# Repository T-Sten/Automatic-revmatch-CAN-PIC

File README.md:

# OPEL-automatic-revmatch-project

Hi! This is a project on creating a device that by plugging into a car's CAN buses and thottle pedal signals, is able to match the
engine RPMs of the lower gear to the wheel speed during a downshift, known as "Revmatching".
The operation of the device is controlled by a PIC16F877A MCU from Microchip.

### Basic idea
The basic idea is as follows: 
Steering wheel button pressed -> Wait for clutch disengagement -> Raise engine RPM to match the lower gear at the current speed and keep it there
-> Wait for clutch engagement -> Stop.

### CAN bus data
From the 3 CAN buses of my 2005 OPEL Vectra C we are interested in 2 of them: 95kbps low speed bus from where driver input can be read 
(such as steering wheel buttons for activating revmatching mode) and the 500kbps bus from where vehicle telematics data can be read
(such as engine RPM, vehicle speed, clucth state etc.). The vehicles CAN buses will be interfaced with a MCP2515 CAN controller IC
and a MCP2551 CAN transciever IC for each of the 2 buses.

### Controlling the throttle
Throttle is controlled by tapping into the (2) throttle pedal potentiometer output wires and with a signal relay we can disconnect
the thottle pedal outputs and start driving the signal voltage with a capacitor smooothed PWM signal to be interpreted by the ECU.
Throttle value is calculated using PID control.

### Additional features
Additional features of the device include displaying current gear on the dashboard with a 7-segment led and a led array for the current RPM. 
These are driven by 2 8-bit shift registers that are interfaced by the MCU with a single differential pair using a RS485 transciever.
Another feature is "welcome actions" where upon unlocking the car doors, horn is briefly activated 3 times
and high beams flashed. This is done by replicating driver input by sending a CAN frame that corresponds to the activation of their driver controls.

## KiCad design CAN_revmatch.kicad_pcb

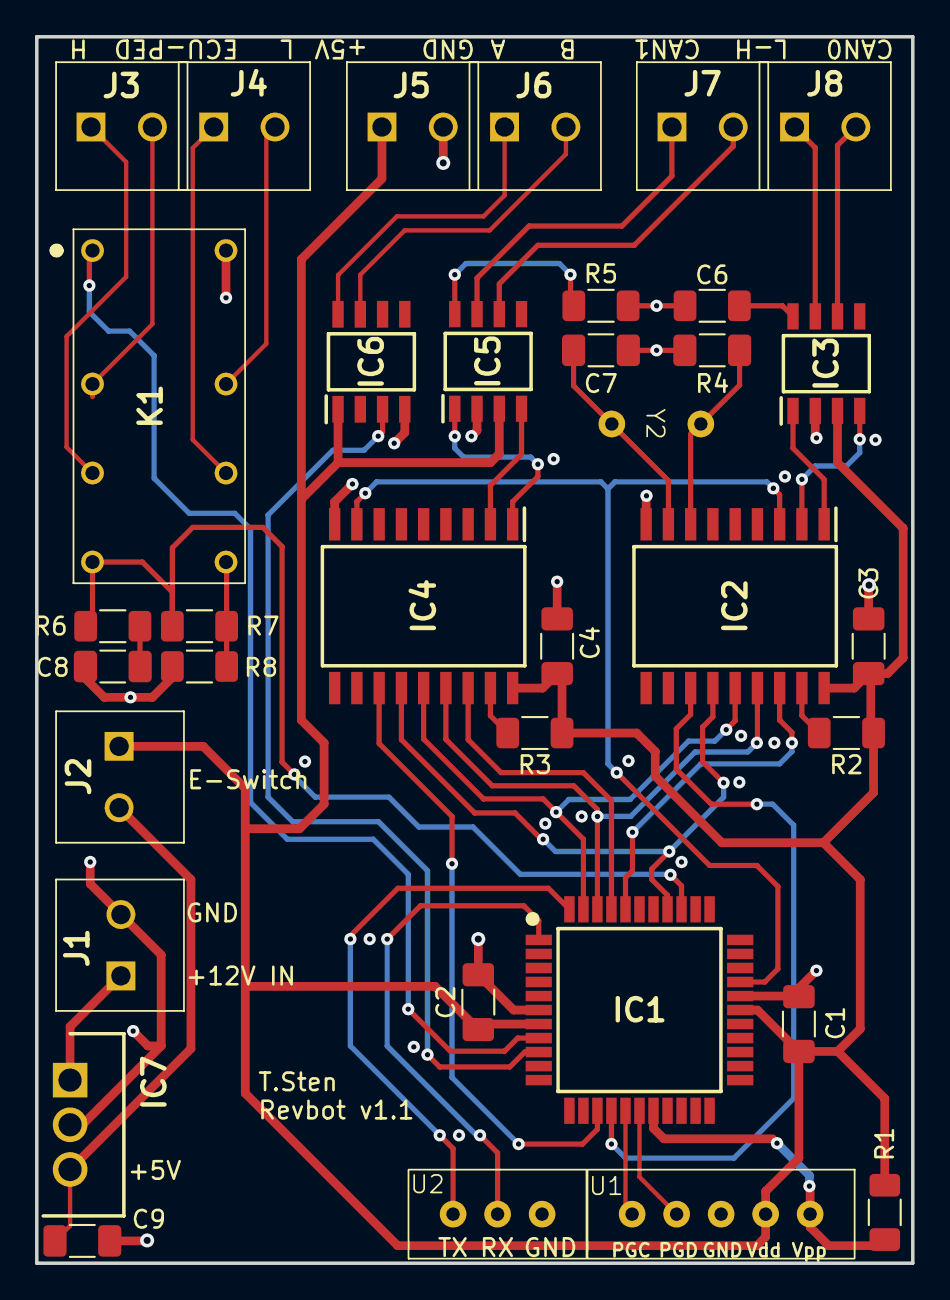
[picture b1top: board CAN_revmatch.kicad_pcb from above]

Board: 4 copper layers, 50.0 x 70.0 mm, 35 parts (0 on the bottom side), 42 nets.

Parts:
C1, C2, C3, C4: 100nF; C_1206_3216Metric_Pad1.33x1.80mm_HandSolder
C6, C7: 22pF; C_1206_3216Metric_Pad1.33x1.80mm_HandSolder
C8: 1uF; C_1206_3216Metric_Pad1.33x1.80mm_HandSolder
C9: 10uF; C_1206_3216Metric_Pad1.33x1.80mm_HandSolder
IC1: PIC16F877A-I_PT; PIC16F877A-SOIC-44pin
IC2, IC4: MCP2515-I_SO; MCP2515_SOIC
IC3, IC5: MCP2551-I_SN; MCP2551_SOIC
IC6: SN75179BDR; Transciever_SN75179BDR
IC7: L7805CV
J1: Power terminal; 1888807
J2: E-Switch; 1888807
J3: Throttle_H; 1888807
J4: Throttle_L; 1888807
J5: RPM/GEAR disp. power; 1888807
J6: RPM/GEAR disp. data; 1888807
J7: CAN1 terminal; 1888807
J8: CAN0 terminal; 1888807
K1: RY-5W-K; RY5WK
R1, R2, R3, R4, R5: 10k; R_1206_3216Metric_Pad1.30x1.75mm_HandSolder
R6, R7, R8: 4.7k; R_1206_3216Metric_Pad1.30x1.75mm_HandSolder
U1: Pickit terminal pin header male; PICKIT_terminal
U2: UART pin header female; UART_terminal
Y2: 8MHz; KIDE

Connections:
+5V: C1.1, C2.1, C3.1, C4.1, IC1.7 (VDD_1), IC1.28 (VDD_2), IC2.18 (VDD), IC3.3 (VDD), IC4.18 (VDD), IC5.3 (VDD), IC6.1 (VCC), J2.1, J5.1, R1.2, R2.1, R3.1, U1.2 (Vdd)
/CLOCK: IC1.30 (OSC1/CLKI), IC2.3 (CLKOUT/SOF), IC4.8 (OSC1)
/CS_CAN0: IC1.40 (RD2/PSP2), IC2.16 (~CS)
/CS_CAN1: IC1.41 (RD3/PSP3), IC4.16 (~CS)
/INT_CAN0: IC1.15 (RB5), IC2.12 (~INT)
/INT_CAN1: IC1.14 (RB4), IC4.12 (~INT)
/MISO: IC1.42 (RC4/SDI/SDA), IC2.15 (SO), IC4.15 (SO)
/MOSI: IC1.43 (RC5/SDO), IC2.14 (SI), IC4.14 (SI)
/PWM: IC1.36 (RC2/CCP1), K1.8, R6.1, R7.2
/RELAY_COIL: IC1.8 (RB0/INT), K1.1
/SCK: IC1.37 (RC3/SCK/SCL), IC2.13 (SCK), IC4.13 (SCK)
/SN75179B_D: IC1.9 (RB1), IC6.3 (D)
GND: C1.2, C2.2, C3.2, C4.2, C6.2, C7.2, C8.2, C9.2, IC1.6 (VSS_1), IC1.29 (VSS_2), IC2.9 (VSS), IC3.2 (VSS), IC4.9 (VSS), IC5.2 (VSS), IC6.4 (GND), IC7.2 (GROUND), J1.2, J5.2, K1.16, R4.2, R5.2, R8.1, U1.3 (GND), U2.3 (GND)
unnamed: C8.1, R6.2
unnamed: IC1.16 (RB6/PGC), U1.5 (PGC)
unnamed: IC1.17 (RB7/PGD), U1.4 (PGD)
unnamed: IC1.44 (RC6/TX/CK), U2.1 (TX)
unnamed: IC1.1 (RC7/RX/DT), U2.2 (RX)
unnamed: IC1.18 (~MCLR/VPP), R1.1, U1.1 (Vpp)
unnamed: C7.1, IC2.8 (OSC1), Y2.2
unnamed: C6.1, IC2.7 (OSC2), Y2.1
unnamed: IC2.2 (RXCAN), IC3.4 (RXD)
unnamed: IC2.1 (TXCAN), IC3.1 (TXD)
unnamed: IC2.17 (~RESET), R2.2
unnamed: IC3.7 (CANH), J8.1
unnamed: IC3.6 (CANL), J8.2
unnamed: IC3.8 (RS), R4.1
unnamed: IC4.2 (RXCAN), IC5.4 (RXD)
unnamed: IC4.1 (TXCAN), IC5.1 (TXD)
unnamed: IC4.17 (~RESET), R3.2
unnamed: IC5.7 (CANH), J7.1
unnamed: IC5.6 (CANL), J7.2
unnamed: IC5.8 (RS), R5.1
unnamed: IC6.8 (A), J6.1
unnamed: IC6.7 (B), J6.2
unnamed: IC7.1 (INPUT), J1.1
unnamed: C9.1, IC7.3 (OUTPUT), J2.2
unnamed: J3.1, K1.6
unnamed: J3.2, K1.4
unnamed: J4.1, K1.11
unnamed: J4.2, K1.13
unnamed: K1.9, R7.1, R8.2

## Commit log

2024-01-29 Init
2024-02-04 Added PCB drawing, schematic update
2024-02-08 Added pcb layout pdf, fixed via mistake
2024-04-25 UART IF added for PC GUI app, corrected can1 bus speed
